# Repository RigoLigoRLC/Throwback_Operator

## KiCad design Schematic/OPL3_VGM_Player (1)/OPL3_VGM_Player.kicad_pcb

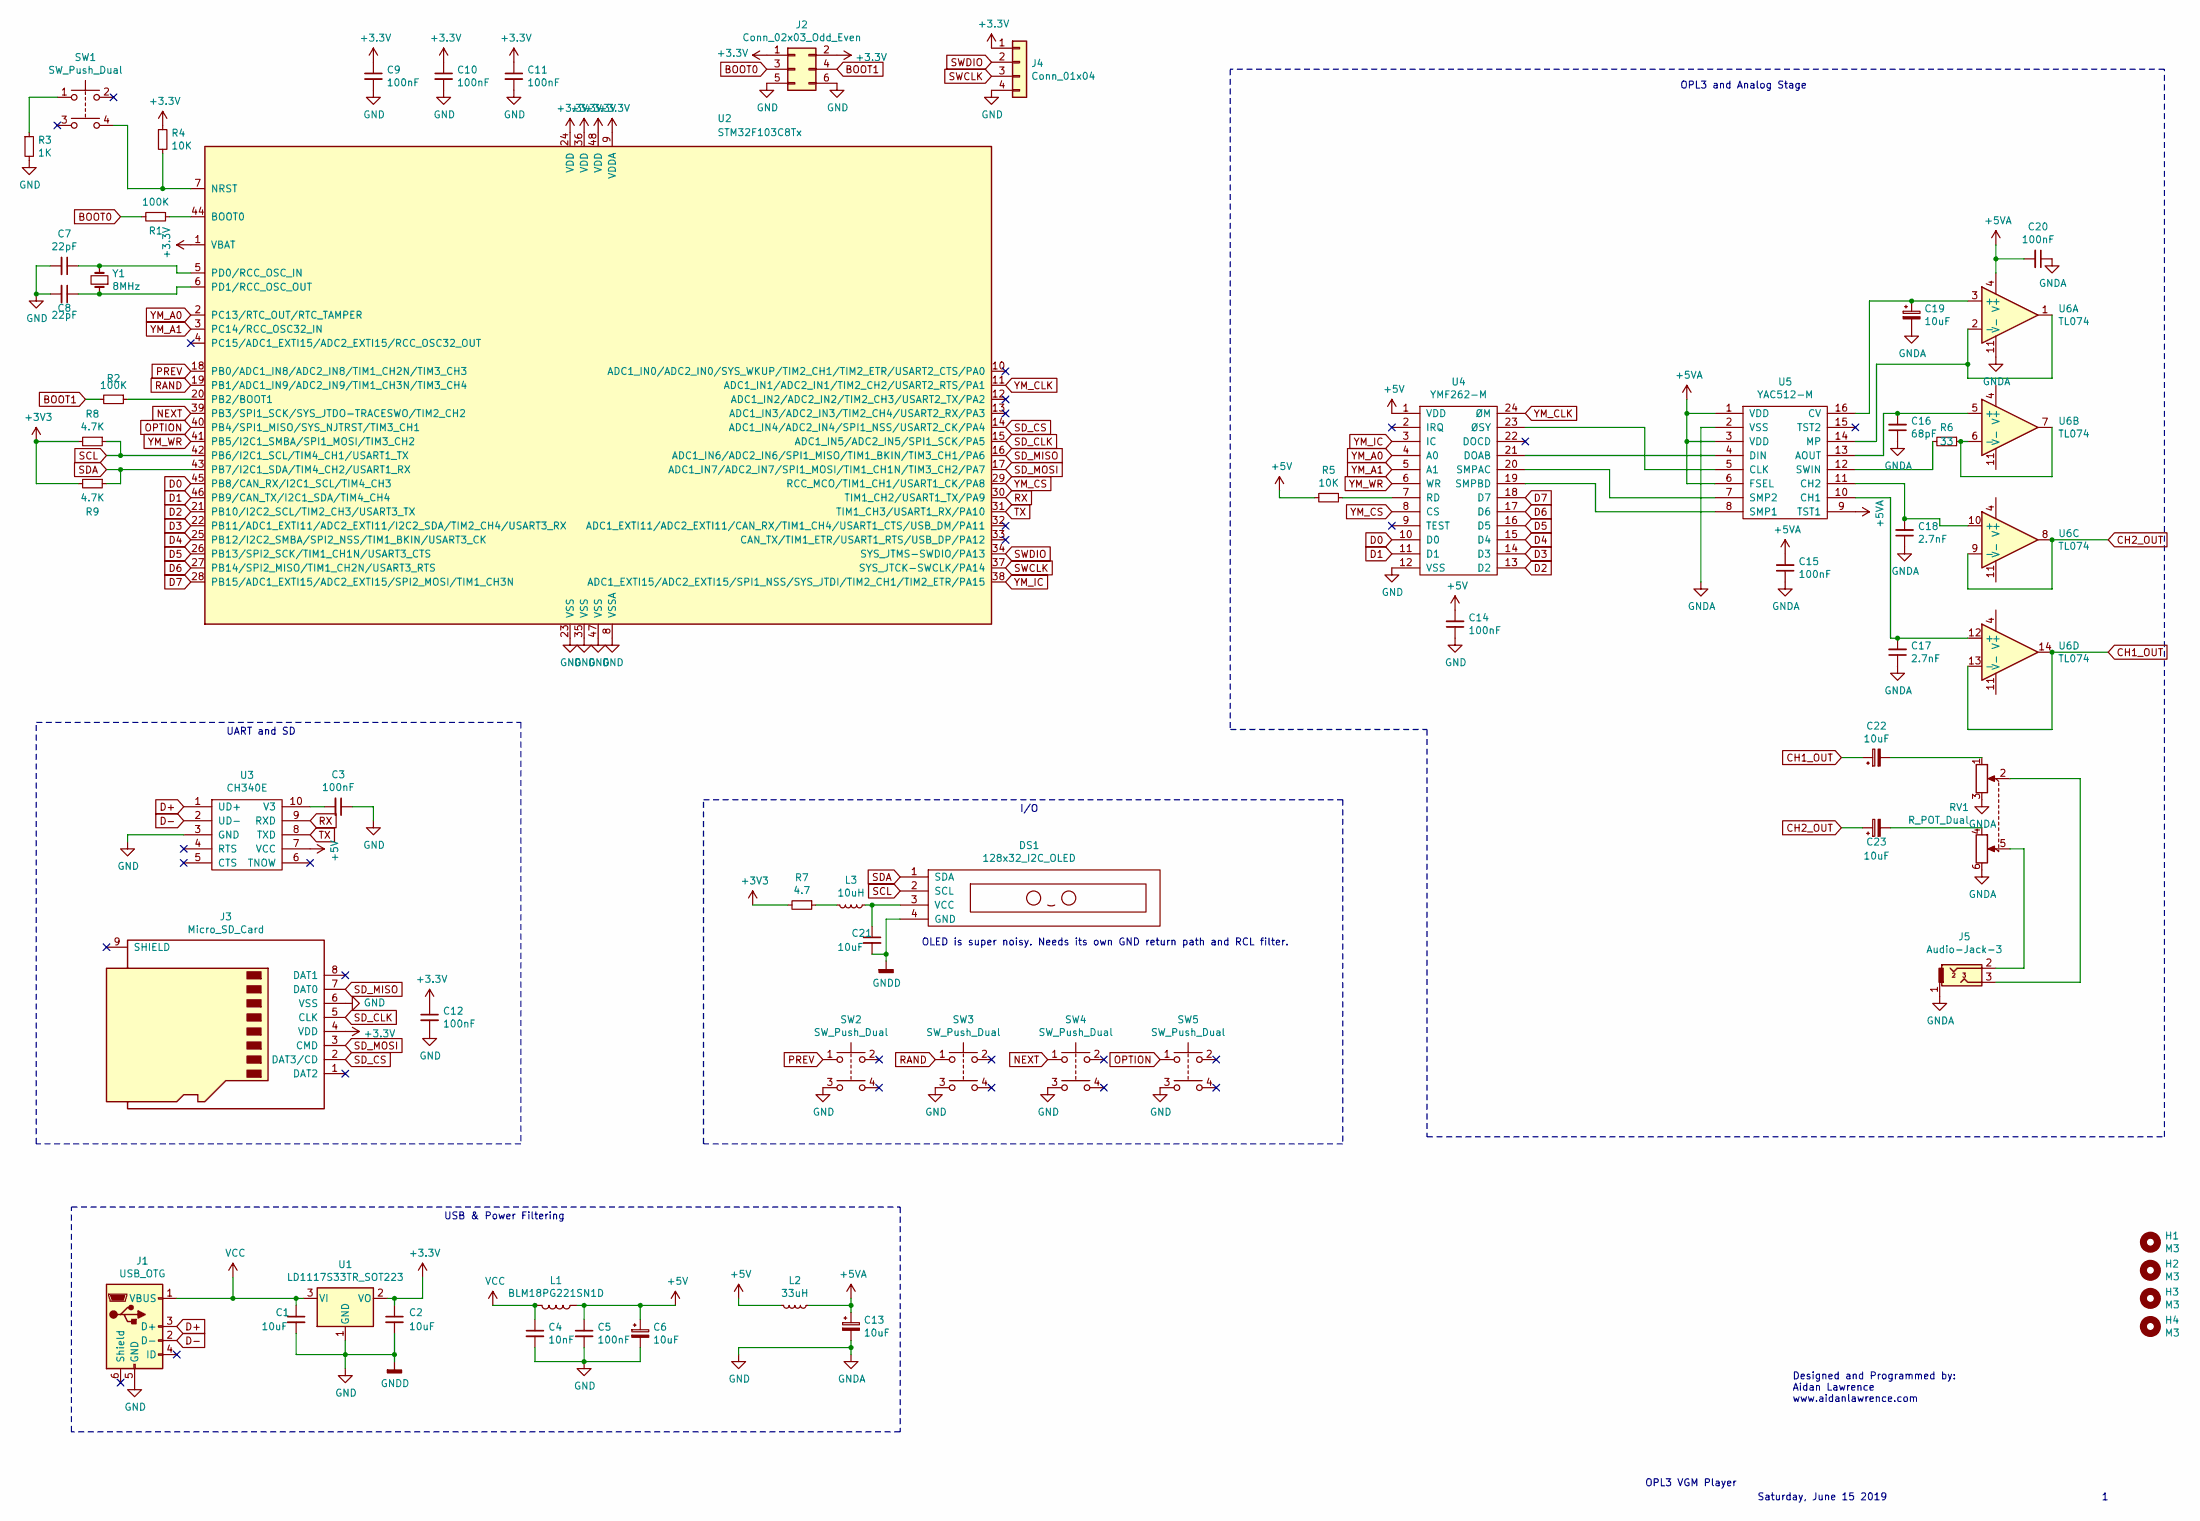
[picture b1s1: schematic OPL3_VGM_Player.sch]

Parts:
C1, C2, C6, C13, C19, C21, C22, C23: 10uF; C_0805_2012Metric_Pad1.15x1.40mm_HandSolder
C3, C5, C9, C10, C11, C12, C14, C15, C20: 100nF; C_0603_1608Metric_Pad1.05x0.95mm_HandSolder
C4: 10nF; C_0603_1608Metric_Pad1.05x0.95mm_HandSolder
C7, C8: 22pF; C_0603_1608Metric_Pad1.05x0.95mm_HandSolder
C16: 68pF; C_0603_1608Metric_Pad1.05x0.95mm_HandSolder
C17, C18: 2.7nF; C_0603_1608Metric_Pad1.05x0.95mm_HandSolder
DS1: 128x32_I2C_OLED; 128x32_OLED_I2C_Module
H1, H2, H3, H4: M3; MountingHole_3.2mm_M3
J1: USB_OTG; USB_Mini-B_Lumberg_2486_01_Horizontal
J2: Conn_02x03_Odd_Even; PinHeader_2x03_P2.54mm_Vertical
J3: Micro_SD_Card; SOFNG_TF_15x15_PUSH_PUSH
J4: Conn_01x04; PinHeader_1x04_P2.54mm_Vertical
J5: Audio-Jack-3; Jack_3.5mm_PJ320B_Horizontal
L1: BLM18PG221SN1D; L_0603_1608Metric_Pad1.05x0.95mm_HandSolder
L2: 33uH; L_4x4
L3: 10uH; L_4x4
R1, R2: 100K; R_0603_1608Metric_Pad1.05x0.95mm_HandSolder
R3: 1K; R_0603_1608Metric_Pad1.05x0.95mm_HandSolder
R4, R5: 10K; R_0603_1608Metric_Pad1.05x0.95mm_HandSolder
R6: 33; R_0603_1608Metric_Pad1.05x0.95mm_HandSolder
R7: 4.7; R_0603_1608Metric_Pad1.05x0.95mm_HandSolder
R8, R9: 4.7K; R_0603_1608Metric_Pad1.05x0.95mm_HandSolder
RV1: R_POT_Dual; Potentiometer_Alps_RK097_Dual_Horizontal
SW1, SW2, SW3, SW4, SW5: SW_Push_Dual; SW_TH_Tactile_Omron_B3F-10xx
U1: LD1117S33TR_SOT223; SOT-223-3_TabPin2
U2: STM32F103C8Tx; LQFP-48_7x7mm_P0.5mm
U3: CH340E; TSSOP-10_3x3mm_P0.5mm
U4: YMF262-M; SOIC-24W_7.5x15.4mm_P1.27mm
U5: YAC512-M; SOIC-16W_5.3x10.2mm_P1.27mm
U6: TL074; SOIC-14_3.9x8.7mm_P1.27mm
Y1: 8MHz; Crystal_HC49-U_Vertical

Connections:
+5V: C5.1, C6.1, C14.2, L1.1, L2.2, R5.2, U3.7 (VCC), U4.1 (VDD)
+5VA: C13.1, C15.2, C20.2, L2.1, U5.1 (VDD), U5.3 (VDD), U5.6 (FSEL), U5.9 (TST1), U6.4 (V+)
BOOT0: J2.3, R1.2
BOOT1: J2.4, R2.2
CH1_OUT: C22.1, U6.13 (-), U6.14
CH2_OUT: C23.1, U6.8, U6.9 (-)
D0: U2.45 (PB8/CAN_RX/I2C1_SCL/TIM4_CH3), U4.10 (D0)
D1: U2.46 (PB9/CAN_TX/I2C1_SDA/TIM4_CH4), U4.11 (D1)
D2: U2.21 (PB10/I2C2_SCL/TIM2_CH3/USART3_TX), U4.13 (D2)
D3: U2.22 (PB11/ADC1_EXTI11/ADC2_EXTI11/I2C2_SDA/T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), U4.14 (D3)
D4: U2.25 (PB12/I2C2_SMBA/SPI2_NSS/TIM1_BKIN/USART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), U4.15 (D4)
D5: U2.26 (PB13/SPI2_SCK/TIM1_CH1N/USART3_CTS), U4.16 (D5)
D6: U2.27 (PB14/SPI2_MISO/TIM1_CH2N/USART3_RTS), U4.17 (D6)
D7: U2.28 (PB15/ADC1_EXTI15/ADC2_EXTI15/SPI2_MOSI/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), U4.18 (D7)
D+: J1.3 (D+), U3.1 (UD+)
D-: J1.2 (D-), U3.2 (UD-)
GND: C1.2, C2.2, C3.1, C4.2, C5.2, C6.2, C7.2, C8.2, C9.2, C10.2, C11.2, C12.2, C13.2, C14.1, C15.1, C16.1, C17.1, C18.1, C19.2, C20.1, C21.2, DS1.4 (GND), J1.5 (GND), J1.6 (Shield), J2.5, J2.6, J3.6 (VSS), J4.4, J5.1, R3.2, RV1.3, RV1.6, SW2.3, SW3.3, SW4.3, SW5.3, U1.1 (GND), U2.8 (VSSA), U2.23 (VSS), U2.35 (VSS), U2.47 (VSS), U3.3 (GND), U4.12 (VSS), U5.2 (VSS), U6.11 (V-)
NEXT: SW4.1, U2.39 (PB3/SPI1_SCK/SYS_JTDO-TRACESWO/TIM2_CH2)
unnamed: C3.2, U3.10 (V3)
unnamed: C7.1, U2.5 (PD0/RCC_OSC_IN), Y1.2
unnamed: C8.1, U2.6 (PD1/RCC_OSC_OUT), Y1.1
unnamed: C16.2, U5.13 (AOUT), U6.5 (+)
unnamed: C17.2, U5.10 (CH1), U6.12 (+)
unnamed: C18.2, U5.11 (CH2), U6.10 (+)
unnamed: C19.1, U5.16 (CV), U6.3 (+)
unnamed: C21.1, DS1.3 (VCC), L3.1
unnamed: C22.2, RV1.1
unnamed: C23.2, RV1.4
unnamed: J5.2, RV1.5
unnamed: J5.3, RV1.2
unnamed: L3.2, R7.1
unnamed: R1.1, U2.44 (BOOT0)
unnamed: R2.1, U2.20 (PB2/BOOT1)
unnamed: R3.1, SW1.1
unnamed: R4.2, SW1.4, U2.7 (NRST)
unnamed: R5.1, U4.7 (RD)
unnamed: R6.1, U6.6 (-), U6.7
unnamed: R6.2, U5.12 (SWIN)
unnamed: U4.19 (SMPBD), U5.8 (SMP1)
unnamed: U4.20 (SMPAC), U5.7 (SMP2)
unnamed: U4.21 (DOAB), U5.4 (DIN)
unnamed: U4.23 (ØSY), U5.5 (CLK)
unnamed: U5.14 (MP), U6.1, U6.2 (-)
OPTION: SW5.1, U2.40 (PB4/SPI1_MISO/SYS_NJTRST/TIM3_CH1)
PREV: SW2.1, U2.18 (PB0/ADC1_IN8/ADC2_IN8/TIM1_CH2N/TIM3_CH3)
RAND: SW3.1, U2.19 (PB1/ADC1_IN9/ADC2_IN9/TIM1_CH3N/TIM3_CH4)
RX: U2.30 (TIM1_CH2/USART1_TX/PA9), U3.9 (RXD)
SCL: DS1.2 (SCL), R8.1, U2.42 (PB6/I2C1_SCL/TIM4_CH1/USART1_TX)
SDA: DS1.1 (SDA), R9.1, U2.43 (PB7/I2C1_SDA/TIM4_CH2/USART1_RX)
SD_CLK: J3.5 (CLK), U2.15 (ADC1_IN5/ADC2_IN5/SPI1_SCK/PA5)
SD_CS: J3.2 (DAT3/CD), U2.14 (ADC1_IN4/ADC2_IN4/SPI1_NSS/USART2_CK/PA4)
SD_MISO: J3.7 (DAT0), U2.16 (ADC1_IN6/ADC2_IN6/SPI1_MISO/TIM1_BKIN/T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)
SD_MOSI: J3.3 (CMD), U2.17 (ADC1_IN7/ADC2_IN7/SPI1_MOSI/TIM1_CH1N/T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)
SWCLK: J4.3, U2.37 (SYS_JTCK-SWCLK/PA14)
SWDIO: J4.2, U2.34 (SYS_JTMS-SWDIO/PA13)
TX: U2.31 (TIM1_CH3/USART1_RX/PA10), U3.8 (TXD)
VCC: C1.1, C4.1, J1.1 (VBUS), L1.2, U1.3 (VI)
YM_A0: U2.2 (PC13/RTC_OUT/RTC_TAMPER), U4.4 (A0)
YM_A1: U2.3 (PC14/RCC_OSC32_IN), U4.5 (A1)
YM_CLK: U2.11 (ADC1_IN1/ADC2_IN1/TIM2_CH2/USART2_RTS/P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), U4.24 (ØM)
YM_CS: U2.29 (RCC_MCO/TIM1_CH1/USART1_CK/PA8), U4.8 (CS)
YM_IC: U2.38 (ADC1_EXTI15/ADC2_EXTI15/SPI1_NSS/SYS_JT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), U4.3 (IC)
YM_WR: U2.41 (PB5/I2C1_SMBA/SPI1_MOSI/TIM3_CH2), U4.6 (WR)

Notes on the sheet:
Designed and Programmed by: Aidan Lawrence www.aidanlawrence.com
OPL3 VGM Player
Saturday, June 15 2019
OLED is super noisy. Needs its own GND return path and RCL filter.
USB & Power Filtering
UART and SD
I/O
OPL3 and Analog Stage

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
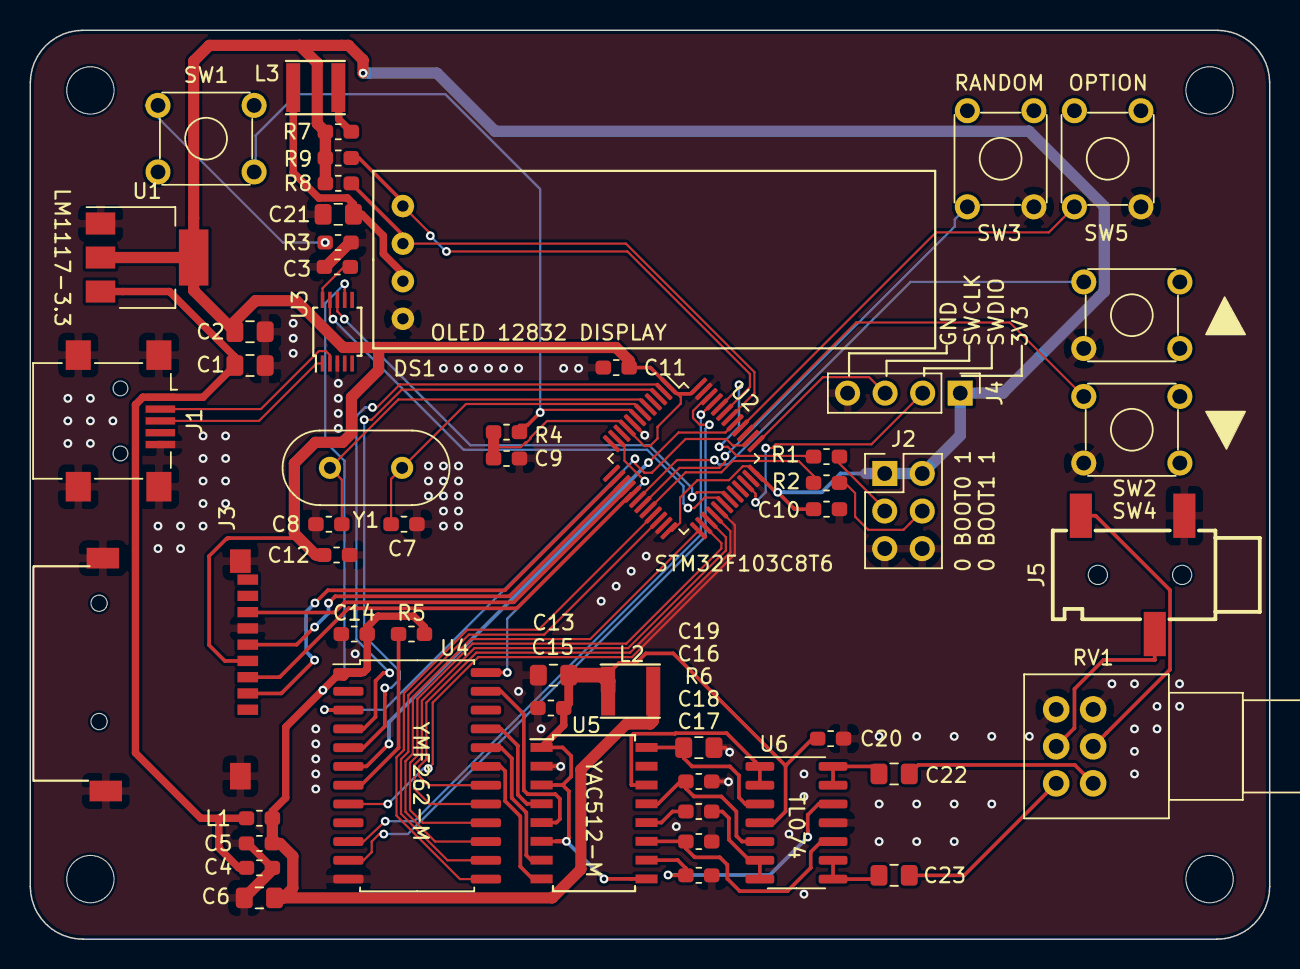
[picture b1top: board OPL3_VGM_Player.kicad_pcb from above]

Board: 2 copper layers, 83.8 x 61.5 mm, 58 parts (0 on the bottom side), 64 nets.

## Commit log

2020-03-11 my layout
2020-03-17 added bom and finished board
